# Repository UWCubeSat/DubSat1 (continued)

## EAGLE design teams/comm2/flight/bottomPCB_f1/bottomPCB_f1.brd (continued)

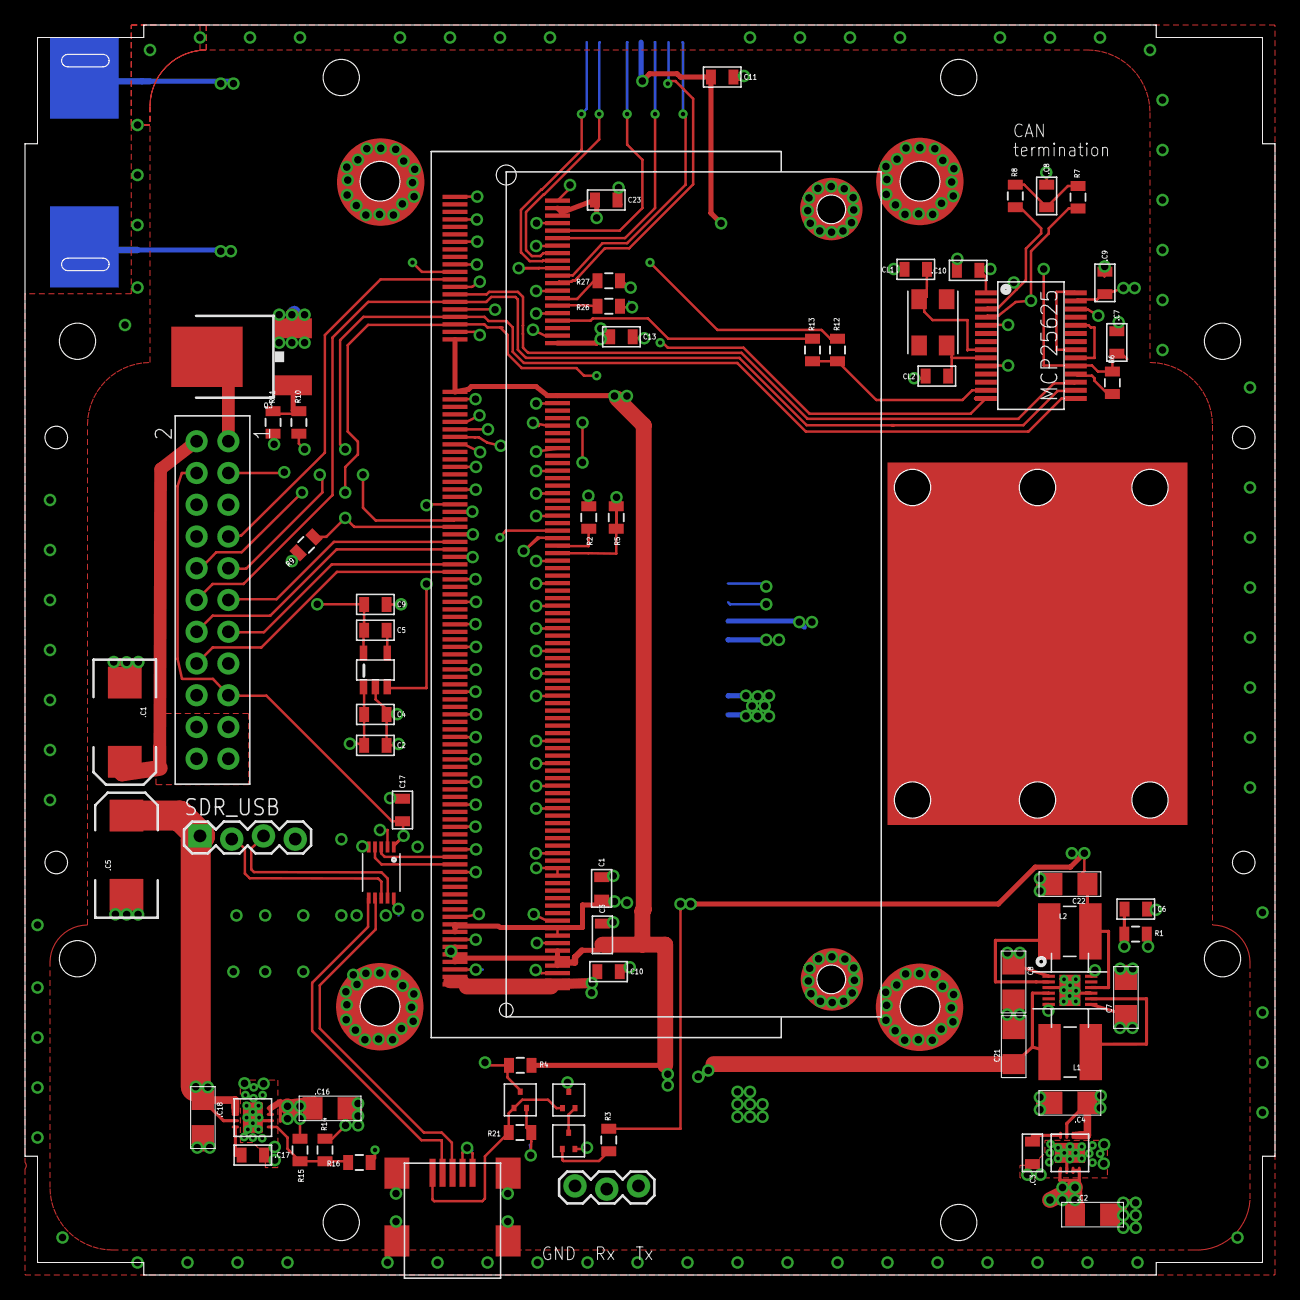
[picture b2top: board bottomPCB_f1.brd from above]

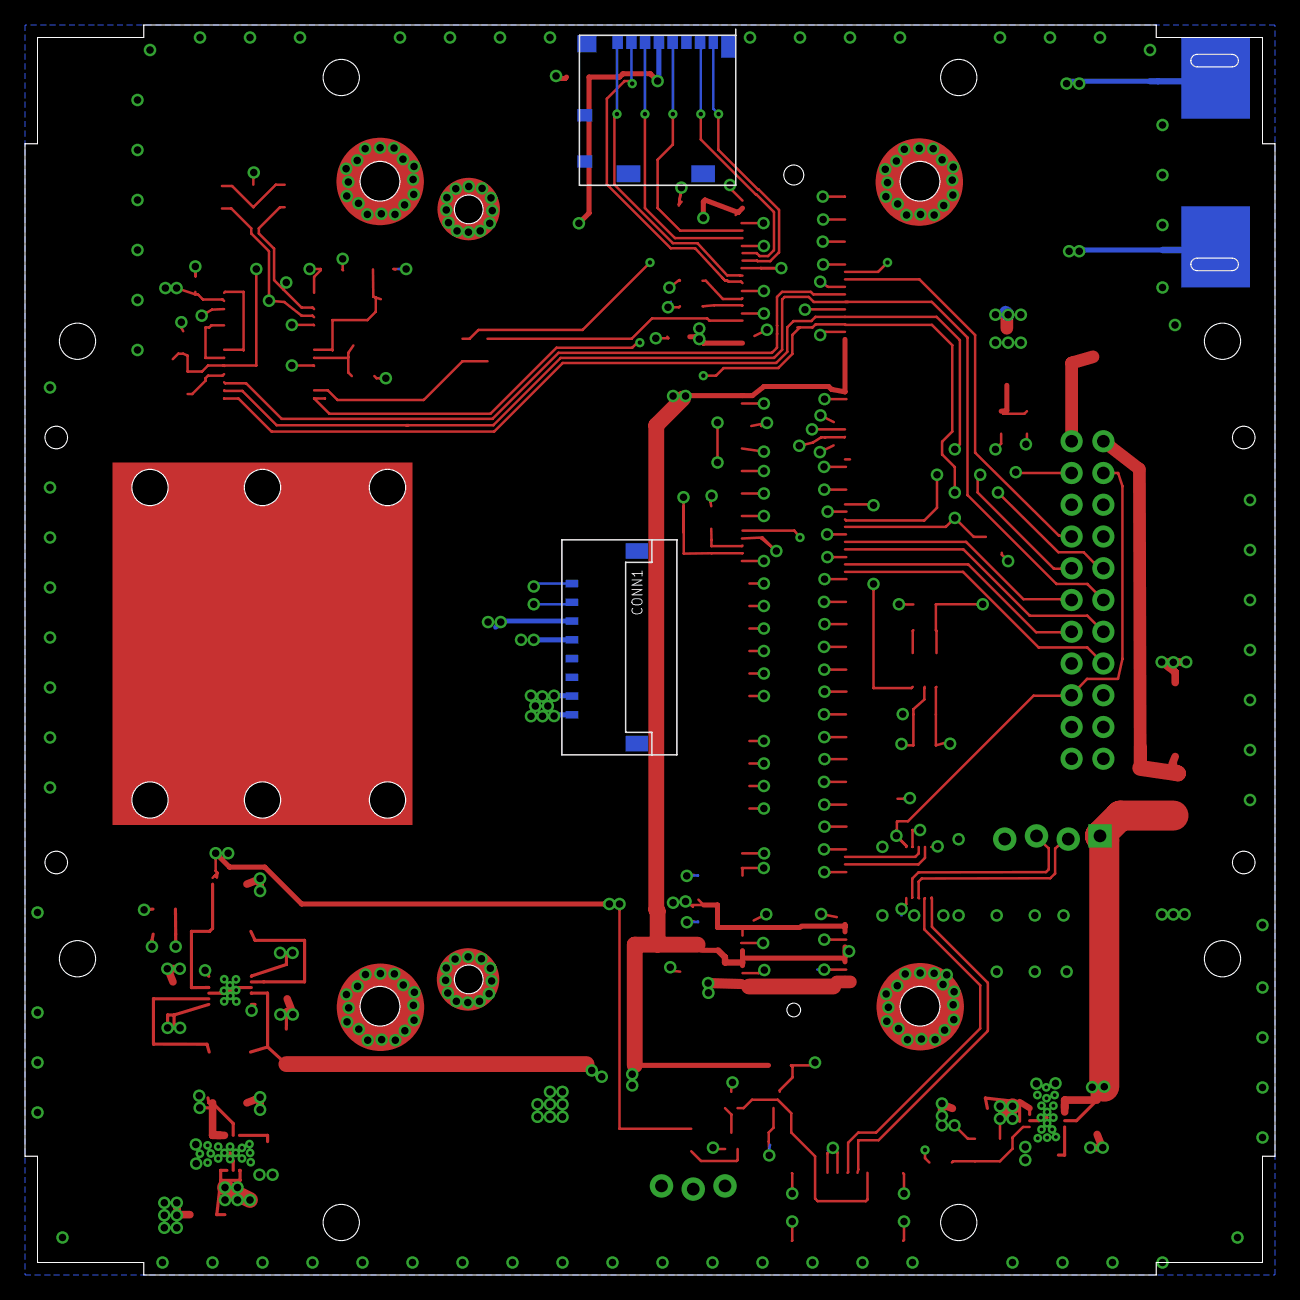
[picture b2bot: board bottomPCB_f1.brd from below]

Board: 4 copper layers, 100.0 x 100.0 mm, 82 parts (2 on the bottom side), 63 nets.

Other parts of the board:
U$1, U$2, U$3, U$4, U$7, U$8, U$9, U$10: #4-40_BOLT_HOLE
U$5, U$6, U$11, U$12: #1-72_BOLT_HOLE
U$23: SDR_B200MINI

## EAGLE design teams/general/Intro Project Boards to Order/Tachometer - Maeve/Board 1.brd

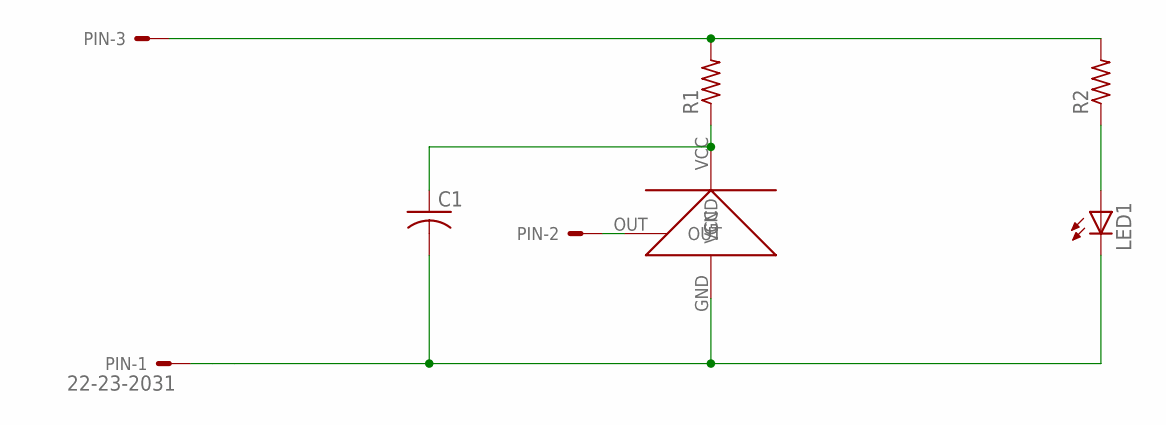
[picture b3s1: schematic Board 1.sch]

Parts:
C1: C-USC0805; C0805
LED1: LED_ELD260; LED_LD260
PIN: 22-23-2031
R1, R2: R-US_R0805; R0805
U$1: TSOP38238

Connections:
GND: C1.2, LED1.K (C), PIN.1, U$1.GND
unnamed: LED1.A, R2.1
unnamed: C1.1, R1.1, U$1.VCC
OUT: PIN.2, U$1.OUT
VCC: PIN.3, R1.2, R2.2

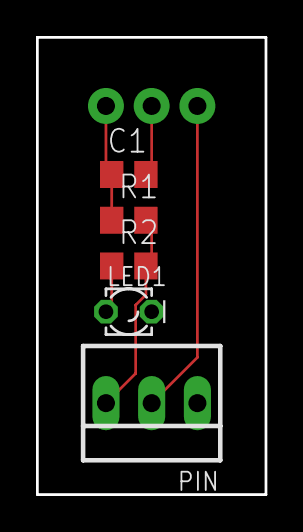
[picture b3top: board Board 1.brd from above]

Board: 2 copper layers, 12.7 x 25.4 mm, 6 parts (0 on the bottom side), 5 nets.

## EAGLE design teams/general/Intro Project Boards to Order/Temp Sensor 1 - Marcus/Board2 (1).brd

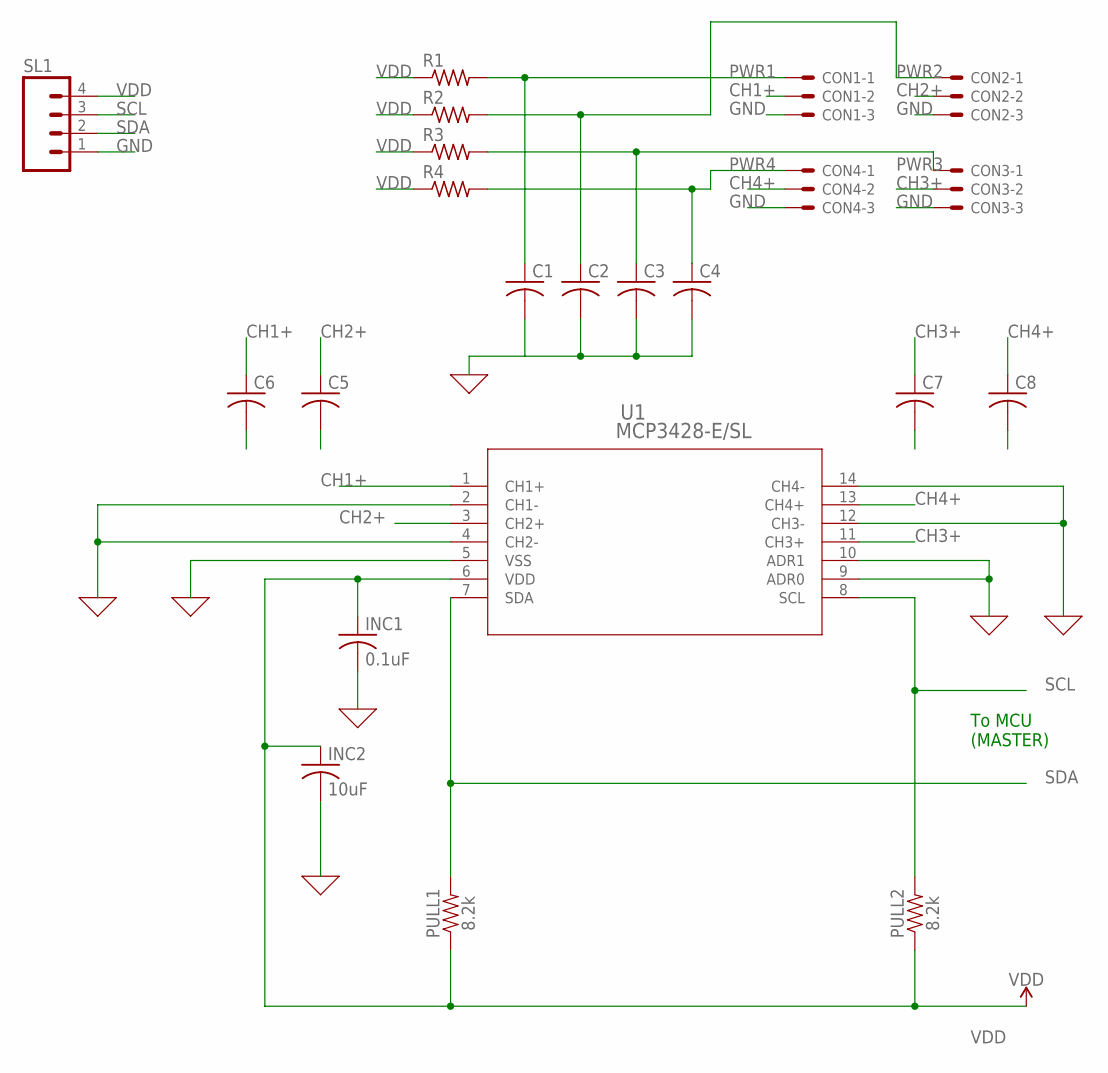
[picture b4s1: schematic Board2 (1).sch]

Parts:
C1, C2, C3, C4, C5, C6, C7, C8: C-USC0805; C0805
CON1, CON2, CON3, CON4: KK-156-3
INC1: 0.1uF; C0805K
INC2: 10uF; C0805K
PULL1, PULL2: 8.2k; 0603
R1, R2, R3, R4: R-US_R0805; R0805
SL1: MA04; 04PA
U1: MCP3428-E/SL; SOIC14-N_MC

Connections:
CH1+: C6.1, CON1.2, U1.1 (CH1+)
CH2+: C5.1, CON2.2, U1.3 (CH2+)
CH3+: C7.1, CON3.2, U1.11 (CH3+)
CH4+: C8.1, CON4.2, U1.13 (CH4+)
GND: C1.2, C2.2, C3.2, C4.2, C5.2, C6.2, C7.2, C8.2, CON1.3, CON2.3, CON3.3, CON4.3, INC1.2, INC2.2, SL1.1, U1.2 (CH1-), U1.4 (CH2-), U1.5 (VSS), U1.9 (ADR0), U1.10 (ADR1), U1.12 (CH3-), U1.14 (CH4-)
PWR1: C1.1, CON1.1, R1.2
PWR2: C2.1, CON2.1, R2.2
PWR3: C3.1, CON3.1, R3.2
PWR4: C4.1, CON4.1, R4.2
SCL: PULL2.2, SL1.3, U1.8 (SCL)
SDA: PULL1.2, SL1.2, U1.7 (SDA)
VDD: INC1.1, INC2.1, PULL1.1, PULL2.1, R1.1, R2.1, R3.1, R4.1, SL1.4, U1.6 (VDD)

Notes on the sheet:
To MCU (MASTER)

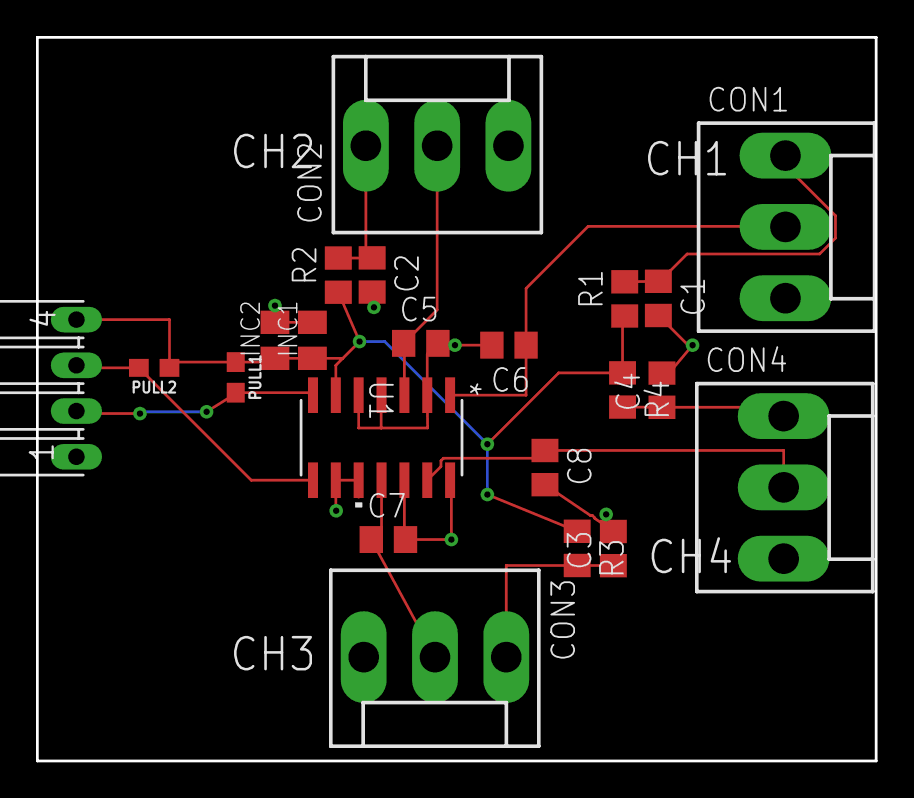
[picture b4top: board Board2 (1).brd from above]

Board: 2 copper layers, 46.6 x 40.2 mm, 22 parts (0 on the bottom side), 12 nets.

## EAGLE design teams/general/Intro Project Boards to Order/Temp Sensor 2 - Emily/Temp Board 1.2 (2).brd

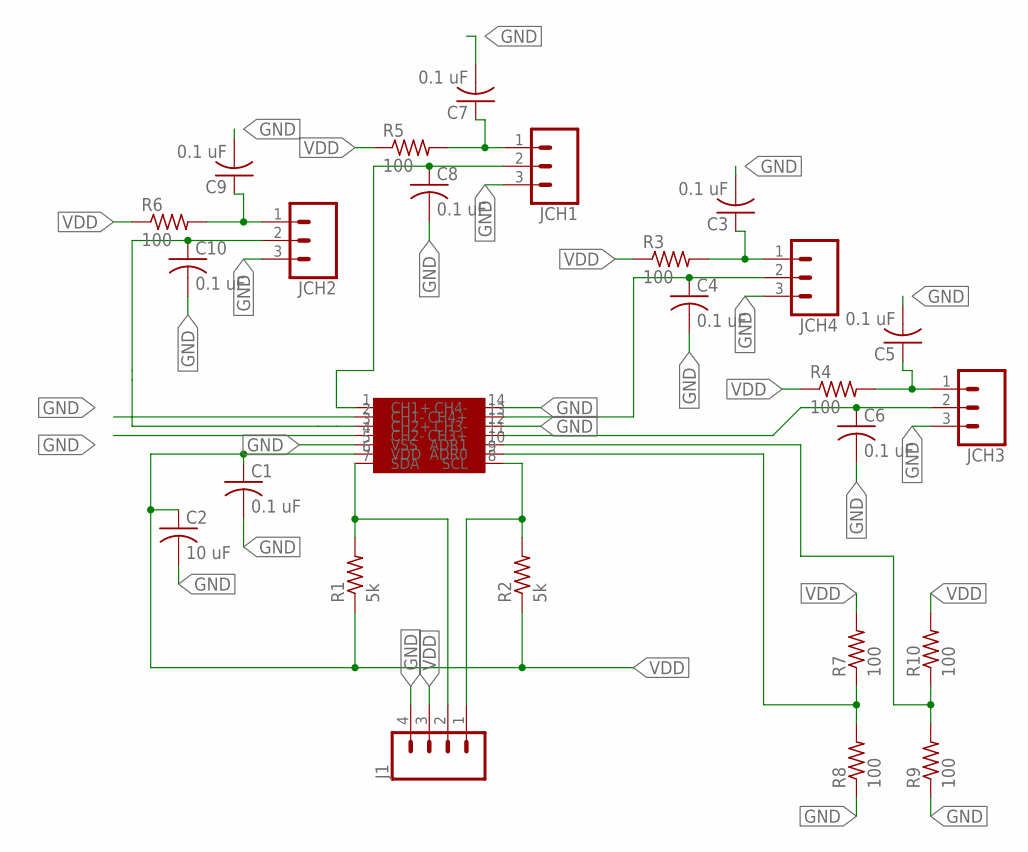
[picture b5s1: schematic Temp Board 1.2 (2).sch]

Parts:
C1, C3, C4, C5, C6, C7, C8, C9, C10: 0.1 uF; C0805
C2: 10 uF; C0805
J1: CONN_04LOCK_LONGPADS; 1X04_LOCK_LONGPADS
JCH1, JCH2, JCH3, JCH4: CONN_03LOCK_LONGPADS; 1X03_LOCK_LONGPADS
R1, R2: 5k; M0805
R3, R4, R5, R6, R7, R8, R9, R10: 100; M0805
U$1: MCP3428A; C04-065B

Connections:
GND: C1.2, C2.2, C3.2, C4.2, C5.2, C6.2, C7.2, C8.2, C9.2, C10.2, J1.4, JCH1.3, JCH2.3, JCH3.3, JCH4.3, R8.1, R9.1, U$1.2 (CH1-), U$1.4 (CH2-), U$1.5 (VSS), U$1.12 (CH3-), U$1.14 (CH4-)
unnamed: C3.1, JCH4.1, R3.2
unnamed: C4.1, JCH4.2, U$1.13 (CH4+)
unnamed: C6.1, JCH3.2, U$1.11 (CH3+)
unnamed: C7.1, JCH1.1, R5.2
unnamed: C8.1, JCH1.2, U$1.1 (CH1+)
unnamed: C9.1, JCH2.1, R6.2
unnamed: C10.1, JCH2.2, U$1.3 (CH2+)
unnamed: R7.1, R8.2, U$1.9 (ADR0)
unnamed: J1.2, R1.2, U$1.7 (SDA)
unnamed: J1.1, R2.2, U$1.8 (SCL)
unnamed: R9.2, R10.1, U$1.10 (ADR1)
unnamed: C5.1, JCH3.1, R4.2
VDD: C1.1, C2.1, J1.3, R1.1, R2.1, R3.1, R4.1, R5.1, R6.1, R7.2, R10.2, U$1.6 (VDD)

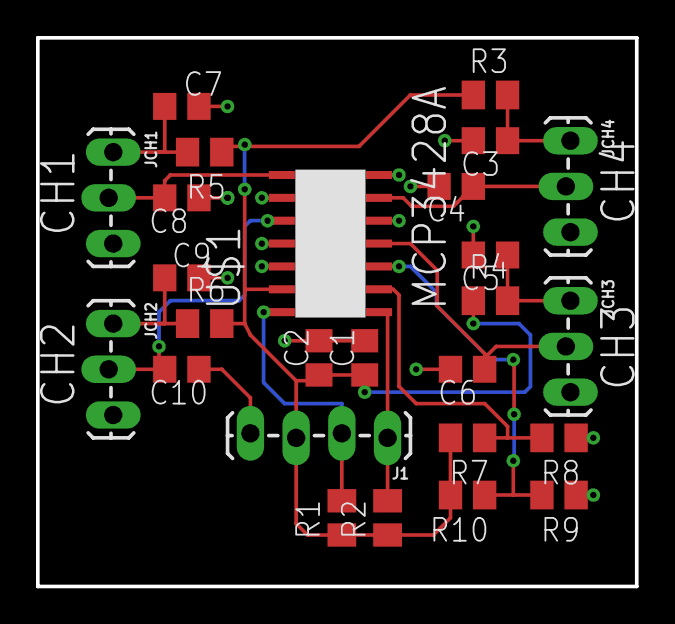
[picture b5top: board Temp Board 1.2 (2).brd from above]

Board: 2 copper layers, 33.3 x 30.5 mm, 26 parts (0 on the bottom side), 14 nets.

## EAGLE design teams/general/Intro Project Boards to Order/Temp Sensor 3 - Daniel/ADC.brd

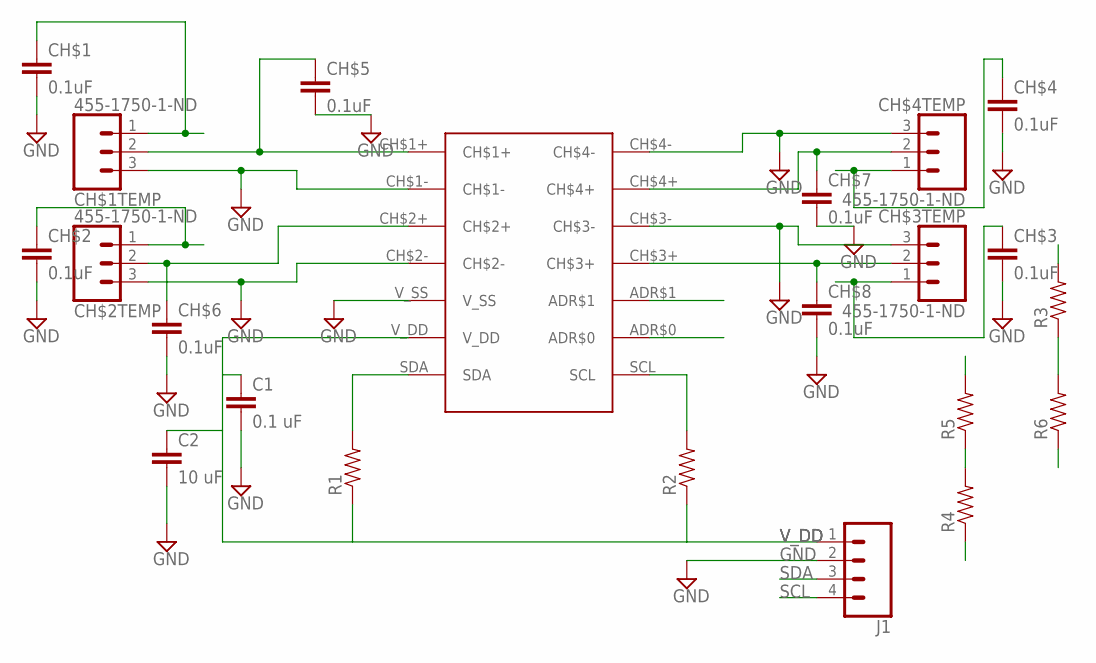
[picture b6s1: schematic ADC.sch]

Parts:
C1: 0.1 uF; 0805
C2: 10 uF; 0805
CH$1, CH$2, CH$3, CH$4, CH$5, CH$6, CH$7, CH$8: 0.1uF; 0805
CH$1TEMP, CH$2TEMP, CH$3TEMP, CH$4TEMP: 455-1750-1-ND; 1X03
J1: CONN_04; 1X04
R1, R2, R3, R4, R5, R6: RESISTOR0805; 0805
U$1: MCP3428-E/SL; MICROCHIP_MCP3428

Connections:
ADR0: R4.2, R5.1, U$1.ADR$0
ADR1: R3.1, R6.2, U$1.ADR$1
CH$2+: CH$2TEMP.2, CH$6.1, U$1.CH$2+
CH$3+: CH$3TEMP.2, CH$8.1, U$1.CH$3+
CH$4+: CH$4TEMP.2, CH$7.1, U$1.CH$4+
GND: C1.2, C2.2, CH$1.2, CH$1TEMP.3, CH$2.2, CH$2TEMP.3, CH$3.2, CH$3TEMP.3, CH$4.2, CH$4TEMP.3, CH$5.2, CH$6.2, CH$7.2, CH$8.2, J1.2, R4.1, R6.1, U$1.CH$1-, U$1.CH$2-, U$1.CH$3-, U$1.CH$4-, U$1.V_SS
unnamed: CH$1TEMP.2, CH$5.1, U$1.CH$1+
SCL: J1.4, R2.2, U$1.SCL
SDA: J1.3, R1.2, U$1.SDA
V_DD: C1.1, C2.1, CH$1.1, CH$1TEMP.1, CH$2.1, CH$2TEMP.1, CH$3.1, CH$3TEMP.1, CH$4.1, CH$4TEMP.1, J1.1, R1.1, R2.1, R3.2, R5.2, U$1.V_DD

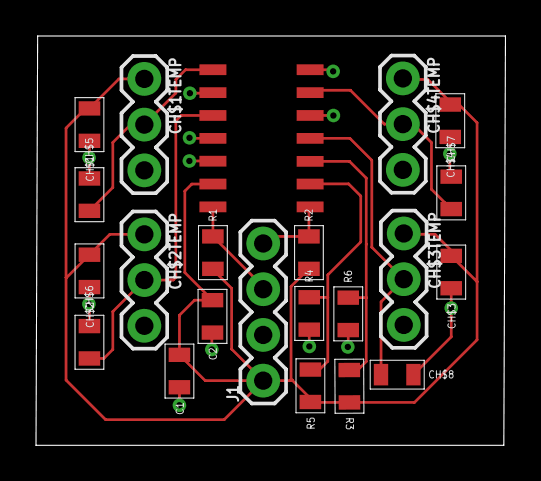
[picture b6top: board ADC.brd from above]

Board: 2 copper layers, 26.1 x 22.7 mm, 22 parts (0 on the bottom side), 10 nets.
